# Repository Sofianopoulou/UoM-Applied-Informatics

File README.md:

# University of Macedonia Assignments Repository

Welcome to my University Assignments Repository! This repository houses assignments and projects I've worked on during my academic journey. The structure of the repository is organized by semesters and courses.

## Structure

- **1st semester**
  - **Algorithms**
    - Best Time to Party (c program)
    - Social Friends (c program)
  - **Procedural Programming**

- **3rd semester**
  - **Object Oriented Programming**
    - Blackjack Game
    - CrimeNet v1
    - CrimeNet v2
    - CrimeNet v3

- **5th semester**
  - **Knowledge Discovery from Databases**
    - Data Editing and Reduction (pp1)
    - 20 Newsgroup Dataset Analysis (pp2)
  - **Web Services and Transactions**
    - 2023 exams solution

- **7th semester**
  - **Design and Programming of Digital Systems**
    - KiCad Designs
    - Tinkercad Designs
  - **Information Retrieval and Search Engines**
    - Lucene Program (pp1)
    - Text Classification (pp2)

## Purpose

This repository serves multiple purposes:
- **Portfolio**: Showcase the diversity of assignments and projects I've undertaken.
- **Learning Progress**: Track my progress and growth in different subjects.
- **Reference**: Provide a resource for others to gain insights or inspiration.

## Usage

Feel free to explore the assignments and projects. If you find anything interesting or have questions, don't hesitate to reach out!

## Contributing

If you see any errors, have suggestions for improvement, or want to contribute, feel free to open an issue or submit a pull request. Contributions are always welcome!

## License

This repository is licensed under the [MIT License](LICENSE). You are free to use the code and materials as you see fit.

Happy coding!

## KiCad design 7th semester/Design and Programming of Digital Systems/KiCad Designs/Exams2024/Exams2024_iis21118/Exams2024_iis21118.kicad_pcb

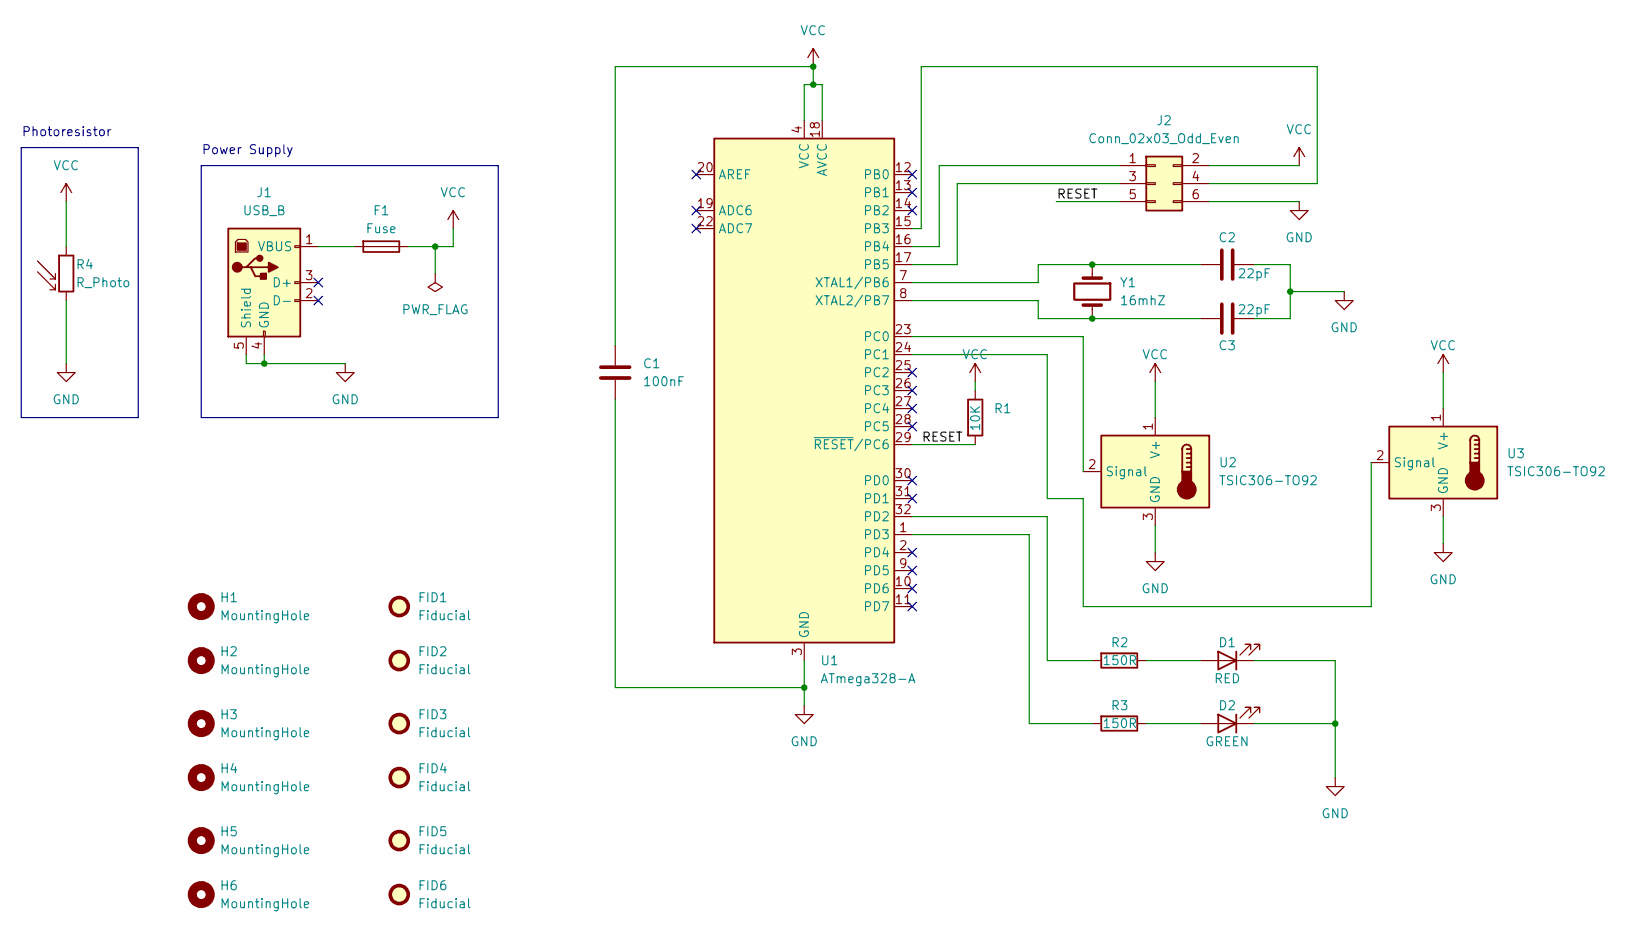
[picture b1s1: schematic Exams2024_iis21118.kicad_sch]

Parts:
C1: 100nF; C_0805_2012Metric
C2, C3: 22pF; C_0805_2012Metric
D1: RED; LED_D5.0mm
D2: GREEN; LED_D5.0mm
F1: Fuse; Fuse_1812_4532Metric
FID1, FID2, FID3, FID4, FID5, FID6: Fiducial; Fiducial_1mm_Mask2mm
H1, H2, H3, H4, H5, H6: MountingHole; MountingHole_3.2mm_M3
J1: USB_B; USB_B_OST_USB-B1HSxx_Horizontal
J2: Conn_02x03_Odd_Even; PinHeader_2x03_P2.54mm_Vertical
R1: 10K; R_0805_2012Metric
R2, R3: 150R; R_0805_2012Metric
R4: R_Photo; R_LDR_5.1x4.3mm_P3.4mm_Vertical
U1: ATmega328-A; TQFP-32_7x7mm_P0.8mm
U2, U3: TSIC306-TO92; TO-92_Inline
Y1: 16mhZ; Crystal_HC49-4H_Vertical

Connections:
/RESET: J2.5, R1.2, U1.29 (~RESET/PC6)
GND: C1.2, C2.2, C3.2, D1.1 (K), D2.1 (K), J1.4 (GND), J1.5 (Shield), J2.6, R4.2, U1.3 (GND), U1.5 (GND), U1.21 (GND), U2.3 (GND), U3.3 (GND)
unnamed: D1.2 (A), R2.1
unnamed: D2.2 (A), R3.1
unnamed: F1.2, J1.1 (VBUS)
unnamed: J2.1, U1.16 (PB4)
unnamed: J2.3, U1.17 (PB5)
unnamed: J2.4, U1.15 (PB3)
unnamed: U1.23 (PC0), U2.2 (Signal)
unnamed: U1.24 (PC1), U3.2 (Signal)
unnamed: R2.2, U1.32 (PD2)
unnamed: R3.2, U1.1 (PD3)
unnamed: C2.1, U1.7 (XTAL1/PB6), Y1.1
unnamed: C3.1, U1.8 (XTAL2/PB7), Y1.2
VCC: C1.1, F1.1, J2.2, R1.1, R4.1, U1.4 (VCC), U1.6 (VCC), U1.18 (AVCC), U2.1 (V+), U3.1 (V+)

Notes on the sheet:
Photoresistor
Power Supply

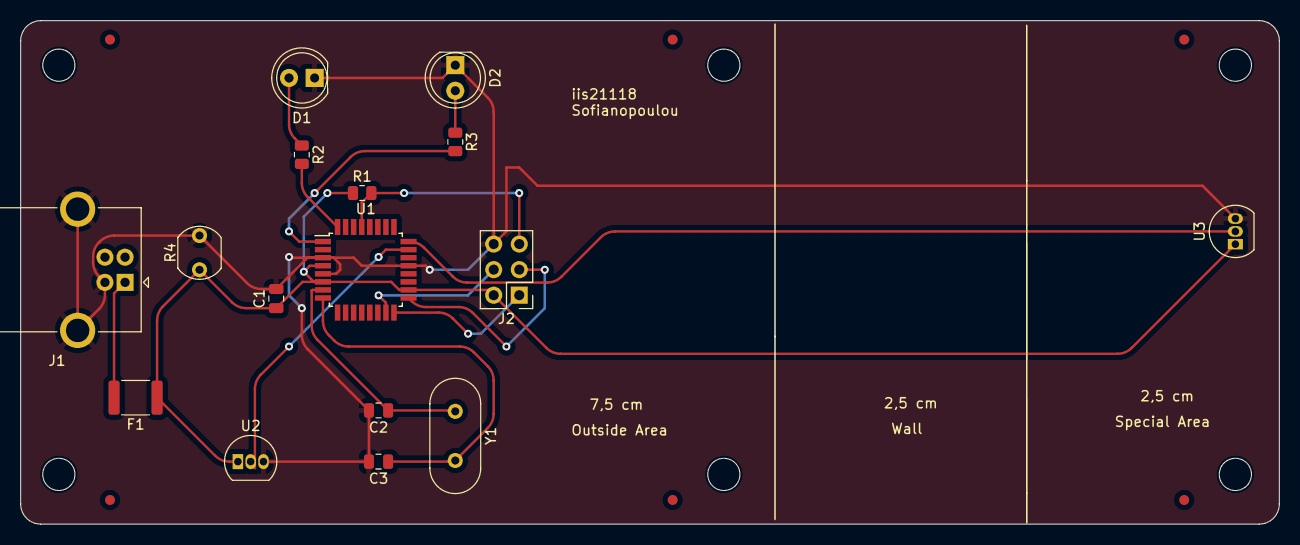
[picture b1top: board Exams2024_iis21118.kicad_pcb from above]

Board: 2 copper layers, 125.0 x 50.0 mm, 28 parts (0 on the bottom side), 15 nets.

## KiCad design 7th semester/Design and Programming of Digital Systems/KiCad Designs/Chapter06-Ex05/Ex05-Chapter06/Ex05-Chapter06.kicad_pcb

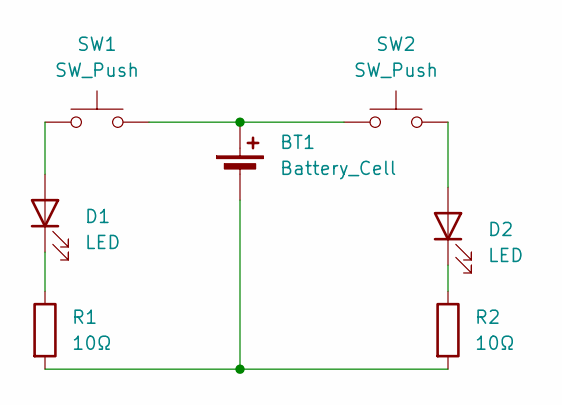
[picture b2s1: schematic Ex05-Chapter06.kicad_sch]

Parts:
BT1: Battery_Cell; BatteryHolder_Keystone_103_1x20mm
D1, D2: LED; LED_D5.0mm_Clear
R1, R2: 10Ω; R_Axial_DIN0207_L6.3mm_D2.5mm_P10.16mm_Horizontal
SW1, SW2: SW_Push; SW_PUSH_6mm_H5mm

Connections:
unnamed: BT1.1 (+), SW1.2, SW2.1
unnamed: BT1.2 (-), R1.2, R2.2
unnamed: D1.2 (A), SW1.1
unnamed: D1.1 (K), R1.1
unnamed: D2.2 (A), SW2.2
unnamed: D2.1 (K), R2.1

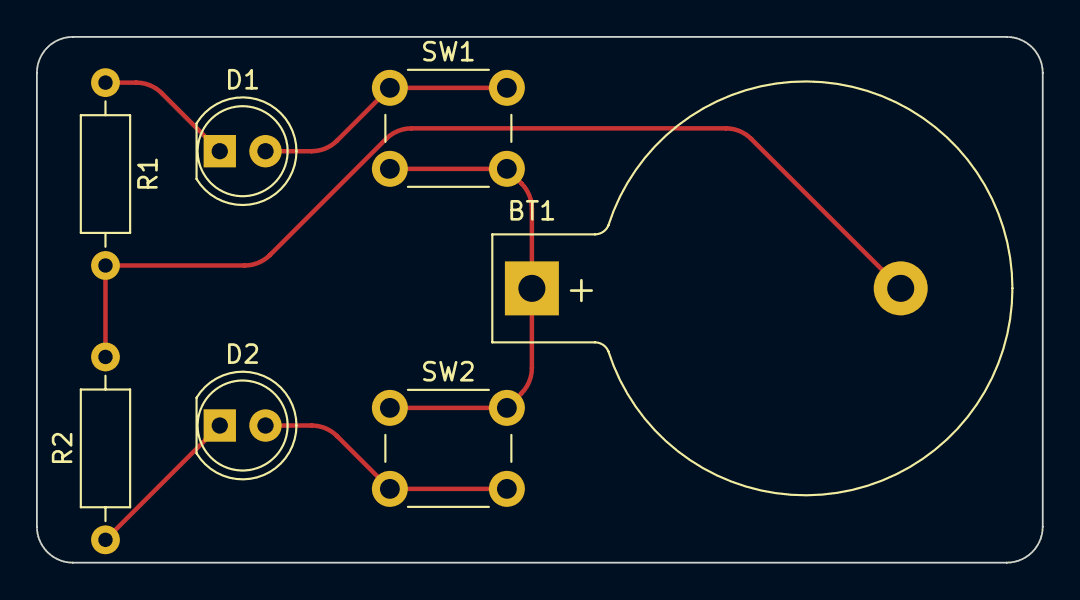
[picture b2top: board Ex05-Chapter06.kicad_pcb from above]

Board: 2 copper layers, 55.9 x 29.2 mm, 7 parts (0 on the bottom side), 6 nets.

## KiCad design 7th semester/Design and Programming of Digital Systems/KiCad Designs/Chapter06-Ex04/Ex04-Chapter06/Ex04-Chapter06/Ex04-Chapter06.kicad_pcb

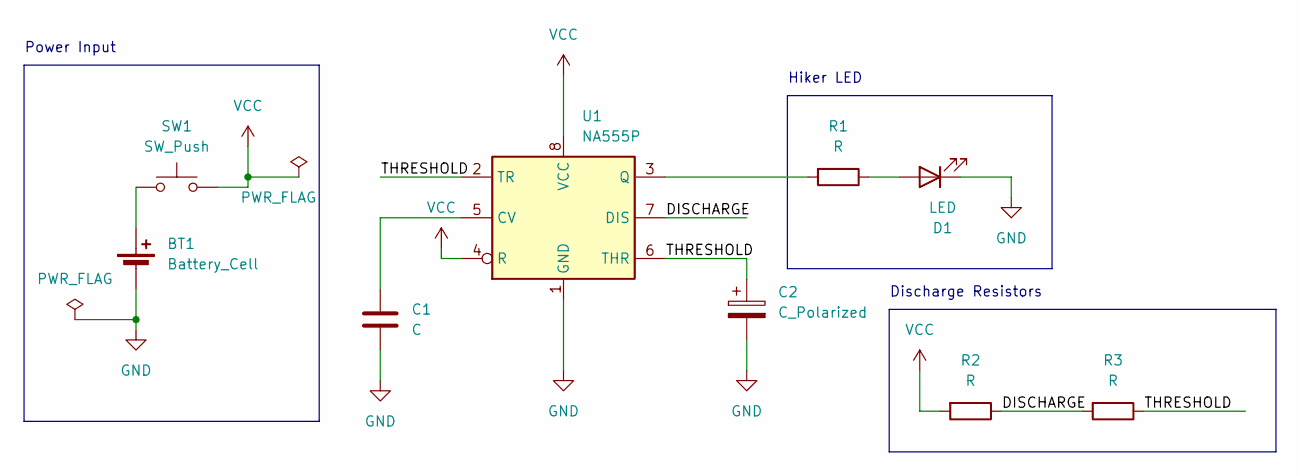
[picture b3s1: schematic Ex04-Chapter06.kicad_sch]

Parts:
BT1: Battery_Cell; BatteryHolder_Keystone_103_1x20mm
C1: C; C_Disc_D6.0mm_W4.4mm_P5.00mm
C2: C_Polarized; CP_Radial_D6.3mm_P2.50mm
D1: LED; LED_D5.0mm_Clear
R1, R2, R3: R; R_Axial_DIN0207_L6.3mm_D2.5mm_P10.16mm_Horizontal
SW1: SW_Push; SW_PUSH_6mm_H5mm
U1: NA555P; DIP-8_W7.62mm

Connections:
/DISCHARGE: R2.1, R3.2, U1.7 (DIS)
/THRESHOLD: C2.1, R3.1, U1.2 (TR), U1.6 (THR)
GND: BT1.2 (-), C1.2, C2.2, D1.1 (K), U1.1 (GND)
unnamed: BT1.1 (+), SW1.1
unnamed: D1.2 (A), R1.1
unnamed: C1.1, U1.5 (CV)
unnamed: R1.2, U1.3 (Q)
VCC: R2.2, SW1.2, U1.4 (R), U1.8 (VCC)

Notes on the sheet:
Hiker LED
Discharge Resistors
Power Input

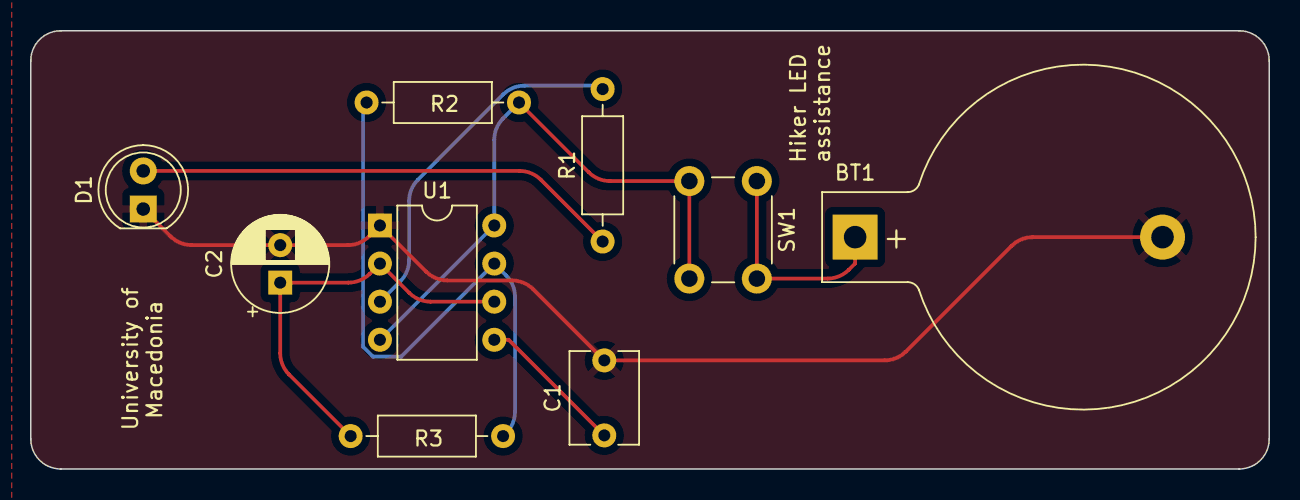
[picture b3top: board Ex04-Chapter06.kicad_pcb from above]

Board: 2 copper layers, 82.6 x 29.2 mm, 9 parts (0 on the bottom side), 8 nets.

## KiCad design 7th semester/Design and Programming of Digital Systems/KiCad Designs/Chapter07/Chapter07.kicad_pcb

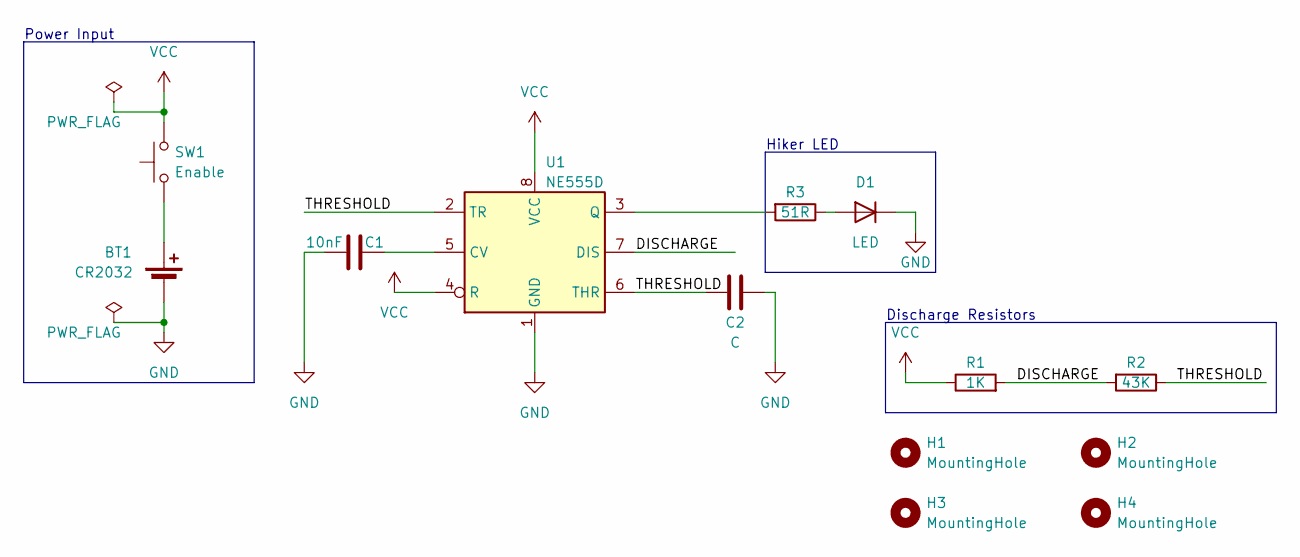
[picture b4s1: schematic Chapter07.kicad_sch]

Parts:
BT1: CR2032; BatteryHolder_Keystone_1060_1x2032
C1: 10nF; C_0805_2012Metric
C2: C; C_1206_3216Metric
D1: LED; LED_0805_2012Metric
H1, H2, H3, H4: MountingHole; MountingHole_3.2mm_M3
R1: 1K; R_0805_2012Metric
R2: 43K; R_0805_2012Metric
R3: 51R; R_0805_2012Metric
SW1: Enable; SW_Push_1P1T_XKB_TS-1187A
U1: NE555D; SOIC-8_3.9x4.9mm_P1.27mm

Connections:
/DISCHARGE: R1.2, R2.2, U1.7 (DIS)
/THRESHOLD: C2.1, R2.1, U1.2 (TR), U1.6 (THR)
GND: BT1.2 (-), C1.1, C2.2, D1.1 (K), U1.1 (GND)
unnamed: BT1.1 (+), SW1.1
unnamed: D1.2 (A), R3.1
unnamed: C1.2, U1.5 (CV)
unnamed: R3.2, U1.3 (Q)
VCC: R1.1, SW1.2, U1.4 (R), U1.8 (VCC)

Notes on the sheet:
Power Input
Hiker LED
Discharge Resistors

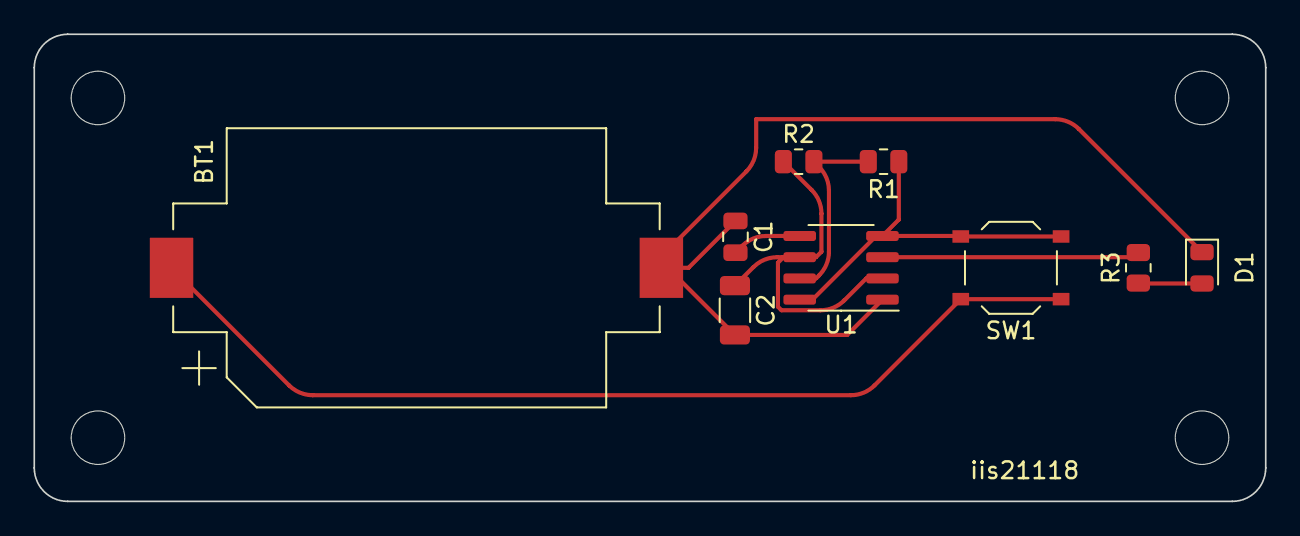
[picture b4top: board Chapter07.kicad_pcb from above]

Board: 2 copper layers, 73.7 x 27.9 mm, 13 parts (0 on the bottom side), 8 nets.

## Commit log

2021-03-31 Create 1st Semester
2021-04-01 Create 2nd Semester
2022-07-08 Create 3rd semester
2022-07-08 Create Object Oriented Programming
2022-12-20 Create 5th semester
2022-12-20 Create Knowledge Discovery from Databases
2022-12-21 Create Programming Project 1
2023-02-18 Create Programming Project 2
2024-01-23 Create Tinkercad Designs
2024-01-31 Update LICENSE
